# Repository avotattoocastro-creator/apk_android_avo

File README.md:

# Evidencia visual iPad

Run 46113092903 · commit 2692a683eb685c10ff76c8f7a6dec165fe4daa5a · rama develop/avo-performance-horse

Capturas del simulador iPad Pro 13 pulgadas (M4) con sesiones de DEMOSTRACIÓN sintéticas.

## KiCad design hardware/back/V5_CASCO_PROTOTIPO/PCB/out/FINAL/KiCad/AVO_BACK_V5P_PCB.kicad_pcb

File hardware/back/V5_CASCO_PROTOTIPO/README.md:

# AVO BACK V5 CASCO · PROTOTIPO A (URTK1.2 por tiras de pines)

**Decisión del usuario (18/11/2026):** antes de pagar la BETA con el ZED-F9P soldado (`../V5_CASCO`, REV B, ≈ 500 € por
el mínimo de 2 placas montadas), se prueba un **casco prototipo** con la misma electrónica pero con el GNSS en una placa
**URTK1.2** (ZED-F9P-04B, la misma del prototipo de la espalda) soldada encima. Si las pruebas son buenas se aprueba
este prototipo o se pasa a la REV B con el ZED integrado como BETA final.

**Estado:** NO VERIFICADO. Diseño en CI; nada fabricado ni impreso. Las cotas de la URTK1.2 salen del plano del anuncio
(y de `../V4/DOCS/INTEGRACION_GNSS.md`): **hay que medirlas con calibre antes de pedir** (ver «Comprobaciones»).

## Qué cambia frente a la REV B (`../V5_CASCO`)

| | REV B (BETA) | PROTOTIPO A |
|---|---|---|
| GNSS | ZED-F9P soldado (LGA), RF de antena en la placa | **URTK1.2** soldada sobre la cara B con 2 tiras de pines (9 + 10, paso 2,54, plástico 2,5 mm) |
| Antena | sobre la cara B de la PCB (plano 51 × 51) | sobre la URTK1.2, encima de una **placa de masa de 52 × 52 × 0,8** (cobre macizo), al U.FL J4 de la URTK1.2 |
| PCB | 51 × 51, tornillos a ±22 | **56 × 56, tornillos a ±24,5** (la URTK1.2 tapaba los de ±22) |
| Cápsula | 56,4 × 56,4 × 24,7 | **61,4 × 61,4 × ≈ 32,1** (≈ 35,6 sobre el casco) — estimado; el CI da la cifra exacta |
| Arranque en caliente del ZED | V_BCKP desde el carril siempre encendido | pila de respaldo de la URTK1.2 (J6) |
| Piezas quitadas | — | U1, R70, C71, L70, R71, D4, J5, C62, C64, C65 y el paso del coaxial H5 |
| Colocación | microSD a la derecha, pogo en el canto inferior | **WROOM en el centro-izquierda, microSD abajo en el centro (tarjeta por el canto inferior, entre D15 y D14), pogo en el canto SUPERIOR** (copa del pogo en la franja +Y del suelo de la cápsula) |
| LED y masa de la antena | 7 LED | **8 LED alineados** (D15/D14 bajo D10/D11; D17/D12 y D16/D13 a la misma altura) · **4 pines de masa J12–J15** en las esquinas, junto a la URTK1.2, soldados a la placa de masa |
| Resto | | igual: ESP32-S3-WROOM-1U-N16R8, cargador, táctil, anillo (**8 LED**: D14 vuelve, a la derecha de la salida de la tarjeta), MAX17048, LSM6DSV16X, microSD, pogo, Hall |

Firmware: **sin cambios de GPIO** (UART1 GPIO5/6, UART2 GPIO3/8, PPS GPIO7, RST GPIO9, ZED_EN GPIO10). El 3,3 V de la
URTK1.2 lo da el RT9080 (se apaga con ZED_EN), como el prototipo de la espalda desde la 3.10.x; 5V sin conectar.

## Conexiones de las tiras (marco de la URTK1.2, vista desde sus componentes)

| Tira | Pines | A la placa |
|---|---|---|
| J10 (9) | GND · 5V · 3V3 · TX2 · RX2 · CS · RX/MOSI · TX/MISO · SCK | GND · — · +3V3_ZED · GPIO3 (330 Ω) · GPIO8 (1 kΩ) · — · GPIO6 (1 kΩ) · GPIO5 (330 Ω) · — |
| J11 (10) | GND · 3V3 · SDA · SCL · FENCE · RTK · PPS · RST · SAFE · INT | GND · +3V3_ZED · — · — · — · — · GPIO7 (330 Ω) · GPIO9 (1 kΩ) · TP13 · — |

«—» = pad aislado: solo sujeta (más soldaduras contra la vibración del galope).

## Montaje
1. Desoldar el SMA J2 de la URTK1.2 (no cabe en la cápsula); la antena va a su U.FL **J4**.
2. Tiras de pines con el plástico **entre** las dos placas; soldar primero a la PCB, luego la URTK1.2 encima
   (componentes hacia arriba). Cortar las puntas a ras por las dos caras (≤ 1,5 mm en la cara F, a ras arriba).
3. Pines de masa J12–J15 (hilo de cobre de 1 mm o pin de tira, ≈ 15 mm) soldados en la PCB. **Placa de masa MACIZA**
   (sin recortes, 18/11 20:15) soldada a los 4 pines con su cara inferior a 5,5 mm sobre los componentes de la URTK1.2:
   pasa por encima de J6, J1, J3 y la clavija del U.FL. El cable de la antena sale de J4 hacia el canto y sube por el
   hueco entre la placa y la pared (≈ 2,3 mm).
4. Antena Taoglas AHP2258 sobre la placa de masa, en el cuadrado serigrafiado, con su cable al U.FL J4.

## Programar y desmontar sin soldar (19/11)
- **USB-C J16** (canto superior, cara F): programar y cargar con la placa **fuera de la cápsula**. El S3 entra solo en
  descarga por USB nativo; si un firmware lo desactiva, puentear TP2 (BOOT) a GND al arrancar. Mejor no conectar el USB-C y
  el pogo a la vez: desde el 23/11 el Schottky D18 impide que el 5 V del pogo entre en el ordenador, pero D± siguen
  en paralelo y el USB puede no enumerar.
- **Batería por coleta:** soldar una vez a BAT+ (J2) / BAT− (J6) un cable corto con conector JST PH 2.0 (el de la celda).
  El empalme va tumbado en la franja del fondo entre la batería y la pared, junto al costado por donde salen los hilos
  de la celda; sujetarlo con una gota de silicona o kapton (el PH no tiene pestillo). **Medir la polaridad** de la
  celda antes de enchufar: en las celdas chinas el rojo no siempre está en el mismo pin.

## Precauciones (revisión independiente 18/11)
- **Kapton** sobre la cara B de la PCB bajo la URTK1.2: las patas de J1, J6 y del SMA quitado apoyarían en la máscara
  sobre el plano de masa.
- **No conectar el USB-C (J1) de la URTK1.2 montada**: su LDO alimentaría +3V3_ZED con el ZED apagado por ZED_EN.
- **Pila J6:** usar la que pida la placa (si J6 se carga desde 3V3, una ML1220 recargable; nunca una CR1220).
- Pines de masa J12–J15: taladro 1,2 mm (pin de tira de 0,64 o hilo de cobre de hasta 1 mm).

## Comprobaciones antes de pedir nada (con la URTK1.2 en la mano)
- **Lo más importante:** medir CADA fila por separado: distancia del primer pin al canto del USB-C (supuesto 12,827 mm)
  y cuál es su pin GND. Si una fila empezara desde el otro canto, se desplazaría 2,54 mm y todas sus redes quedarían
  mal. Medidas de la placa (43,434 × 43,688) y distancia entre filas (40,64).
- Diámetro, altura y posición del portapilas J6 (el CAD supone Ø13 × 5 mm).
- Que **J4 llegue al ZED** con J2 quitado (continuidad / prueba con la antena).
- Altura del portapilas J6 con pila, de J1 (USB-C) y de J3, y lo que sobresale por debajo (debe ser < 2,5 mm).
- Versión del ZED en u-center (MON-VER): **ZED-F9P-04B**.

## Ficheros
- `PCB/fuente/` — generador (copia de la REV B con las diferencias marcadas «PROTOTIPO A»); las librerías grandes
  (`lib_easyeda`, `3d`, `hojas`) son enlaces a las de `../V5_CASCO/PCB/fuente`.
- `PCB/fuente/placa_masa.py` → `PCB/PLACA_MASA/`: Gerber y taladros de la placa de masa (2 capas, 0,8 mm) y su
  geometría para el CAD.
- `CAD/avo_casco_v5p.py` — cápsula; CI `build-back-v5p-cad.yml`. PCB: CI `build-back-v5p-pcb.yml`.

## Auditoría externa (22–23/11/2026)
- NTC RT2 sobre el centro de la batería, a 25,9 mm del BQ24072 (antes 3,0 mm: medía el calor del cargador).
- Anillo LED a 4,28 V (R25 620k / R26 100k), como la REV B: margen del DIN de 3,3 V ≈ 0,3 V.
- Schottky D18 (B5819W SL) en el VBUS del USB-C J16. Revisar su giro en la vista previa de JLC (cátodo = pad 1).
- Detalle: `docs/REGISTRO_DE_CAMBIOS.md` (23/11) y el documento de auditoría del proyecto.

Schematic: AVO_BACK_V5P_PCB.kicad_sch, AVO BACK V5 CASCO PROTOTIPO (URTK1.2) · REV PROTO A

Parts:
C18, C26, C27, C28, C36, C66, C67: 1u; C_0402_1005Metric; LCSC C52923
C19, C20, C21, C40, C60, C98: 10u 25V; C_0603_1608Metric; LCSC C96446
C22, C24, C35, C61, C99: 22u 10V; C_0805_2012Metric; LCSC C45783
C25, C34, C37, C38, C41, C42, C63, C68, C80, C90, C91, C92, C93, C94, C95, C96, C97: 100n; C_0402_1005Metric; LCSC C1525
C69: 22p; C_0402_1005Metric; LCSC C1555; not fitted
D2, D3: TVS 5 V; D_SOD-323; MPN PESD5V0S1BA; LCSC C2827694
D5, D6: BAT54C; SOT-23; MPN BAT54C; LCSC C2135
D10, D11, D12, D13, D14, D15, D16, D17: SK6812SIDE-A; AVO_SK6812SIDE-A_4.0x1.6mm; MPN SK6812SIDE-A (OPSCO); LCSC C5378721
D18: B5819W; D_SOD-123; MPN B5819W SL; LCSC C8598
F1, F2: PTC 1,5 A; Fuse_1206_3216Metric; MPN SMD1206P150TF; LCSC C20802
J2: BAT +; WirePad_D1.7_Drill0.9
J3: microSD DM3AT; microSD_HC_Hirose_DM3AT-SF-PEJM5; MPN DM3AT-SF-PEJM5; LCSC C114218
J6: BAT −; WirePad_D1.7_Drill0.9
J7: TÁCTIL; WirePad_D1.7_Drill0.9
J10: URTK1.2 9 pines; AVO_URTK1.2_Tira_1x09_P2.54
J11: URTK1.2 10 pines; AVO_URTK1.2_Tira_1x10_P2.54
J12, J13, J14, J15: GND PLACA ANTENA; WirePad_D2.0_Drill1.2
J16: USB-C programación; USB_C_Receptacle_HRO_TYPE-C-31-M-12; MPN TYPE-C-31-M-12 (HRO); LCSC C165948
L71: 1 µH; IND-SMD_L2.0-W1.6_FNR2016XXS; MPN WPN201610U1R0MT (Sunlord); LCSC C97016
P1: POGO VBUS; WirePad_D1.7_Drill0.9
P2: POGO D−; WirePad_D1.7_Drill0.9
P3: POGO D+; WirePad_D1.7_Drill0.9
P4: POGO GND; WirePad_D1.7_Drill0.9
P5: POGO AUX; WirePad_D1.7_Drill0.9
Q4, Q7: AO3401A; SOT-23; LCSC C15127
R6, R23: 1k5; R_0402_1005Metric; LCSC C25867
R7, R25: 2k; R_0402_1005Metric; LCSC C4109
R8, R9, R10, R13, R15, R21, R27, R40, R60: 100k; R_0402_1005Metric; LCSC C25741
R11, R17, R20, R41, R42, R43, R44, R45, R47: 10k; R_0402_1005Metric; LCSC C25744
R12: 68k; R_0402_1005Metric; LCSC C36871
R14, R32, R33: 1M; R_0402_1005Metric; LCSC C26083
R16, R22, R50, R51, R52: 1k; R_0402_1005Metric; LCSC C11702
R18, R19, R46: 22R; R_0402_1005Metric; LCSC C25092
R24, R26, R53, R54, R55: 330R; R_0402_1005Metric; LCSC C25104
R28, R29: 2k2; R_0402_1005Metric; LCSC C25879
R30, R31: 5k1; R_0402_1005Metric; LCSC C25905
RT2: NTC 10k B3380; R_0402_1005Metric; MPN NCP15XH103F03RC; LCSC C77131
TP1: EN; TestPoint_Pad_D1.0mm
TP2: BOOT; TestPoint_Pad_D1.0mm
TP3: GND; TestPoint_Pad_D1.0mm
TP4: TXD0; TestPoint_Pad_D1.0mm
TP5: RXD0; TestPoint_Pad_D1.0mm
TP6: 3V3; TestPoint_Pad_D1.0mm
TP7: VBAT; TestPoint_Pad_D1.0mm
TP8: VSYS; TestPoint_Pad_D1.0mm
TP9: 3V3_ZED; TestPoint_Pad_D1.0mm
TP10: 3V3_AON; TestPoint_Pad_D1.0mm
TP12: VLED; TestPoint_Pad_D1.0mm
TP13: SAFEBOOT; TestPoint_Pad_D1.0mm
U2: BQ24072RGTR; VQFN-16-1EP_3x3mm_P0.5mm_EP1.68x1.68mm_ThermalVias; MPN BQ24072RGTR; LCSC C140288
U3: TLV75733PDBVR; SOT-23-5; MPN TLV75733PDBVR; LCSC C485517
U4: ESP32-S3-WROOM-1U-N16R8; ESP32-S3-WROOM-1U; MPN ESP32-S3-WROOM-1U-N16R8; LCSC C3013946
U6: USBLC6-2SC6; SOT-23-6; LCSC C7519
U7: RT9080-33GJ5; SOT-23-5; MPN RT9080-33GJ5; LCSC C841192
U8: DRV5032FA; SOT-23; MPN DRV5032FADBZR; LCSC C140921
U9: XC6206P332MR; SOT-23; MPN XC6206P332MR-G (Torex); LCSC C5446
U10: TTP223-BA6-TD; SOT-23-6; MPN TTP223-BA6-TD (TDSEMIC); LCSC C42422127
U11: TPS61023DRLR; SOT-563_L1.6-W1.2-P0.50-LS1.6-BR; MPN TPS61023DRLR (TI); LCSC C919459
U12: MAX17048G+T10; TDFN-8_L2.0-W2.0-P0.50-BL-EP1.2; MPN MAX17048G+T10 (Analog Devices); LCSC C2682616
U13: LSM6DSV16X; ST_LGA-14L_2.5x3mm_P0.5mm; MPN LSM6DSV16XTR (ST); LCSC C5267406

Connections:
+3V3: C22.1, C24.1, C25.1, C26.1, C37.1, C38.1, C42.2, C80.1, Q4.2 (S), R9.2, R10.2, R11.2, R28.2, R29.2, R40.2, TP6.1, U3.5 (OUT), U4.2 (3V3), U8.1 (VCC), U13.5 (VDDIO), U13.8 (VDD), U13.12 (CS)
+3V3_AON: C67.1, C68.1, TP10.1, U9.2 (VOUT), U10.5 (VDD)
+3V3_SD: C40.1, C41.1, J3.4 (VDD), Q4.3 (D), R41.2, R42.2, R43.2, R44.2, R45.2
+3V3_ZED: C61.1, C63.1, J10.3 (3V3), J11.2 (3V3), TP9.1, U7.5 (VOUT)
BAT_ADC: C34.1, R32.2, R33.1, U4.38 (IO2 BAT_ADC)
BAT_F: F1.2, Q7.3 (D)
BAT_G: Q7.1 (G), R13.1
BAT_IN: F1.1, J2.1
BOOT: TP2.1, U4.27 (IO0 BOOT)
CHG_EN2: R8.1, U2.5 (EN2)
CHG_ILIM: R7.1, U2.12 (ILIM)
CHG_ISET: R6.1, U2.16 (ISET)
CHG_PG: R9.1, U2.7 (PGOOD), U4.31 (IO38 CHG_PG)
CHG_STAT: R10.1, U2.9 (CHG), U4.32 (IO39 CHG_STAT)
CHG_TMR: R12.1, U2.14 (TMR)
CHG_TS: RT2.1, U2.1 (TS)
EN: C27.1, R11.1, TP1.1, U4.3 (EN EN)
EN_3V3: C28.1, D5.3 (K), D6.3 (K), R14.1, U3.3 (EN)
GND: C18.2, C19.2, C20.2, C21.2, C22.2, C24.2, C25.2, C26.2, C27.2, C28.2, C34.2, C35.2, C36.2, C37.2, C38.2, C40.2, C41.2, C60.2, C61.2, C63.2, C66.2, C67.2, C68.2, C69.2, C80.2, C90.2, C91.2, C92.2, C93.2, C94.2, C95.2, C96.2, C97.2, C98.2, C99.2, D2.2 (A), D3.2 (A), D10.4 (GND), D11.4 (GND), D12.4 (GND), D13.4 (GND), D14.4 (GND), D15.4 (GND), D16.4 (GND), D17.4 (GND), J3.6 (VSS), J3.10 (DET_COM), J3.11 (SHELL), J6.1, J10.1 (GND), J11.1 (GND), J12.1, J13.1, J14.1, J15.1, J16.A1 (GND), J16.A12 (GND), J16.B1 (GND), J16.B12 (GND), J16.S1 (SHIELD), P4.1, R6.2, R7.2, R12.2, R13.2, R14.2, R15.2, R21.2, R23.2, R26.2, R27.2, R30.2, R31.2, R33.2, R60.2, RT2.2, TP3.1, U2.4 (CE), U2.6 (EN1), U2.8 (VSS), U2.15 (TD), U2.17 (EP), U3.2 (GND), U4.1 (GND), U4.40 (GND), U4.41 (GND), U6.2 (GND), U7.2 (GND), U8.3 (GND), U9.1 (VSS), U10.2 (VSS), U10.4 (AHLB), U10.6 (TOG), U11.4 (GND), U12.1 (CTG), U12.4 (GND), U12.6 (QSTRT), U12.9 (EP), U13.1 (SDO/SA0), U13.2 (SDx), U13.3 (SCx), U13.6 (GND), U13.7 (GND)
HALL: U4.39 (IO1 HALL), U8.2 (OUT)
I2C_SCL: R28.1, U4.34 (IO41 I2C_SCL), U12.7 (SCL), U13.13 (SCL)
I2C_SDA: R29.1, U4.35 (IO42 I2C_SDA), U12.8 (SDA), U13.14 (SDA)
IMU_INT1: U4.4 (IO4 IMU_INT1), U13.4 (INT1)
LED_D1: D10.1 (DIN), R24.2
LED_D2: D10.3 (DOUT), D11.1 (DIN)
LED_D3: D11.3 (DOUT), D12.1 (DIN)
LED_D4: D12.3 (DOUT), D13.1 (DIN)
LED_D5: D13.3 (DOUT), D14.1 (DIN)
LED_D6: D14.3 (DOUT), D15.1 (DIN)
LED_D7: D15.3 (DOUT), D16.1 (DIN)
LED_D8: D16.3 (DOUT), D17.1 (DIN)
LED_DIN_S3: R24.1, U4.24 (IO47 LED_DIN_S3)
LED_PWR: R27.1, U4.25 (IO48 LED_PWR), U11.2 (EN)
POGO_AUX: R20.2, R21.1, U4.33 (IO40 POGO_AUX)
POGO_AUX_C: D3.1 (K), P5.1, R20.1
POGO_VBUS: D2.1 (K), D18.1 (K), F2.1, P1.1
PWR_HOLD: D5.2 (A2), R15.1, U4.16 (IO46 PWR_HOLD)
S3_TX1: R50.1, U4.6 (IO6 S3_TX1)
S3_TX2: R51.1, U4.12 (IO8 S3_TX2)
S3_ZRST: R52.1, U4.17 (IO9 S3_ZRST)
SD_CLK: J3.5 (CLK), R46.2
SD_CLK0: R46.1, U4.20 (IO12 SD_CLK0)
SD_CMD: J3.3 (CMD), R41.1, U4.21 (IO13 SD_CMD)
SD_D0: J3.7 (DAT0), R42.1, U4.22 (IO14 SD_D0)
SD_D1: J3.8 (DAT1), R43.1, U4.8 (IO15 SD_D1)
SD_D2: J3.1 (DAT2), R44.1, U4.9 (IO16 SD_D2)
SD_D3: J3.2 (CD/DAT3), R45.1, U4.10 (IO17 SD_D3)
SD_G: C42.1, Q4.1 (G), R40.1, R47.2
SD_PWR_N: R47.1, U4.23 (IO21 SD_PWR_N)
TOUCH_E: J7.1, R16.1
TOUCH_I: C69.1, R16.2, U10.3 (I)
TOUCH_OUT: D5.1 (A1), R17.1, U10.1 (Q)
TOUCH_SENSE: R17.2, U4.19 (IO11 TOUCH_SENSE)
U0RX: TP5.1, U4.36 (RXD0 U0RX)
U0TX: TP4.1, U4.37 (TXD0 U0TX)
USBC_CC1: J16.A5 (CC1), R30.1
USBC_CC2: J16.B5 (CC2), R31.1
USBC_VBUS: D18.2 (A), J16.A4 (VBUS), J16.A9 (VBUS), J16.B4 (VBUS), J16.B9 (VBUS)
USB_DM: R19.2, U4.13 (IO19 D- USB_DM)
USB_DM_C: J16.A7 (D-), J16.B7 (D-), P2.1, R19.1, U6.3 (IO2), U6.4 (IO2)
USB_DP: R18.2, U4.14 (IO20 D+ USB_DP)
USB_DP_C: J16.A6 (D+), J16.B6 (D+), P3.1, R18.1, U6.1 (IO1), U6.6 (IO1)
VBAT: C20.1, C36.1, C66.1, Q7.2 (S), R32.1, TP7.1, U2.2 (BAT), U2.3 (BAT), U9.3 (VIN), U12.2 (CELL), U12.3 (VDD)
VBUS: C18.1, F2.2, R22.1, U2.13 (IN), U6.5 (VBUS)
VBUS_DET: D6.1 (A1), R22.2, R23.1, U4.11 (IO18 VBUS_DET)
VLED: C90.1, C91.1, C92.1, C93.1, C94.1, C95.1, C96.1, C97.1, C99.1, D10.2 (VDD), D11.2 (VDD), D12.2 (VDD), D13.2 (VDD), D14.2 (VDD), D15.2 (VDD), D16.2 (VDD), D17.2 (VDD), R25.1, TP12.1, U11.6 (VOUT)
VLED_FB: R25.2, R26.1, U11.1 (FB)
VLED_SW: L71.2, U11.5 (SW)
VSYS: C19.1, C21.1, C35.1, C60.1, C98.1, L71.1, R8.2, TP8.1, U2.10 (OUT), U2.11 (OUT), U3.1 (IN), U7.1 (VIN), U11.3 (VIN)
ZED_EN: R60.1, U4.18 (IO10 ZED_EN), U7.3 (EN)
ZED_PPS: R55.2, U4.7 (IO7 ZED_PPS)
ZED_PPS_C: J11.7 (PPS), R55.1
ZED_RST: J11.8 (RST), R52.2
ZED_RX1: J10.7 (RX/MOSI), R50.2
ZED_RX2: J10.5 (RX2), R51.2
ZED_SAFEBOOT: J11.9 (SAFE), TP13.1
ZED_TX1: R53.2, U4.5 (IO5 ZED_TX1)
ZED_TX1_C: J10.8 (TX/MISO), R53.1
ZED_TX2: R54.2, U4.15 (IO3 ZED_TX2)
ZED_TX2_C: J10.4 (TX2), R54.1

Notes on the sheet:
POGO MAGNÉTICO DE 5 CONTACTOS (por hilos): VBUS · D− · D+ · GND · AUX — carga y USB con el PC · ESD
ENCENDIDO Y APAGADO TOTAL: OR de diodos al EN del 3,3 V (táctil · POWER_HOLD GPIO46 · VBUS)
ANILLO DE LUZ: 7 × SK6812SIDE-A (GPIO47) a 4,3 V con elevador TPS61023 (EN = GPIO48, salida desconectada con EN = 0)
microSD (SDMMC 4 bits) · alimentación conmutada
GNSS EN MÓDULO URTK1.2 (ZED-F9P) POR TIRAS DE PINES: 3,3 V propio con EN (RT9080) · UART1 · UART2 · PPS · RESET
BATERÍA (hilos soldados) · PTC · medida por ADC
CARGADOR CON CAMINO DE POTENCIA (BQ24072) · batería 1S ≥ 2000 mAh
3,3 V PRINCIPAL (TLV75733P, 1 A) · EN = OR(táctil, POWER_HOLD, VBUS)
ESP32-S3-WROOM-1U-N16R8 (16 MB + PSRAM 8 MB) · BLE móvil + ESP-NOW cinchas · arranque
SENSOR HALL DRV5032 · encendido al poner la cápsula en la base del casco
3,3 V SIEMPRE ENCENDIDO (XC6206, ≈ 1 µA): táctil (la URTK1.2 lleva su pila de respaldo)
TÁCTIL SELLADO (TTP223, activo alto, directo) · electrodo por hilo · lectura en GPIO11
MEDIDOR DE BATERÍA MAX17048 (0x36, ModelGauge, ≈ 3 µA)
IMU LSM6DSV16X (0x6A) · INT1 → GPIO4 (despierta por movimiento)
BUS I²C (GPIO41 SCL · GPIO42 SDA, 400 kHz)
PUNTOS DE PRUEBA
Generado por fuente/avo_back_v5_pcb.py (mismo origen de datos que la placa). Las conexiones son etiquetas globales: dos pines con la misma etiqueta están unidos.

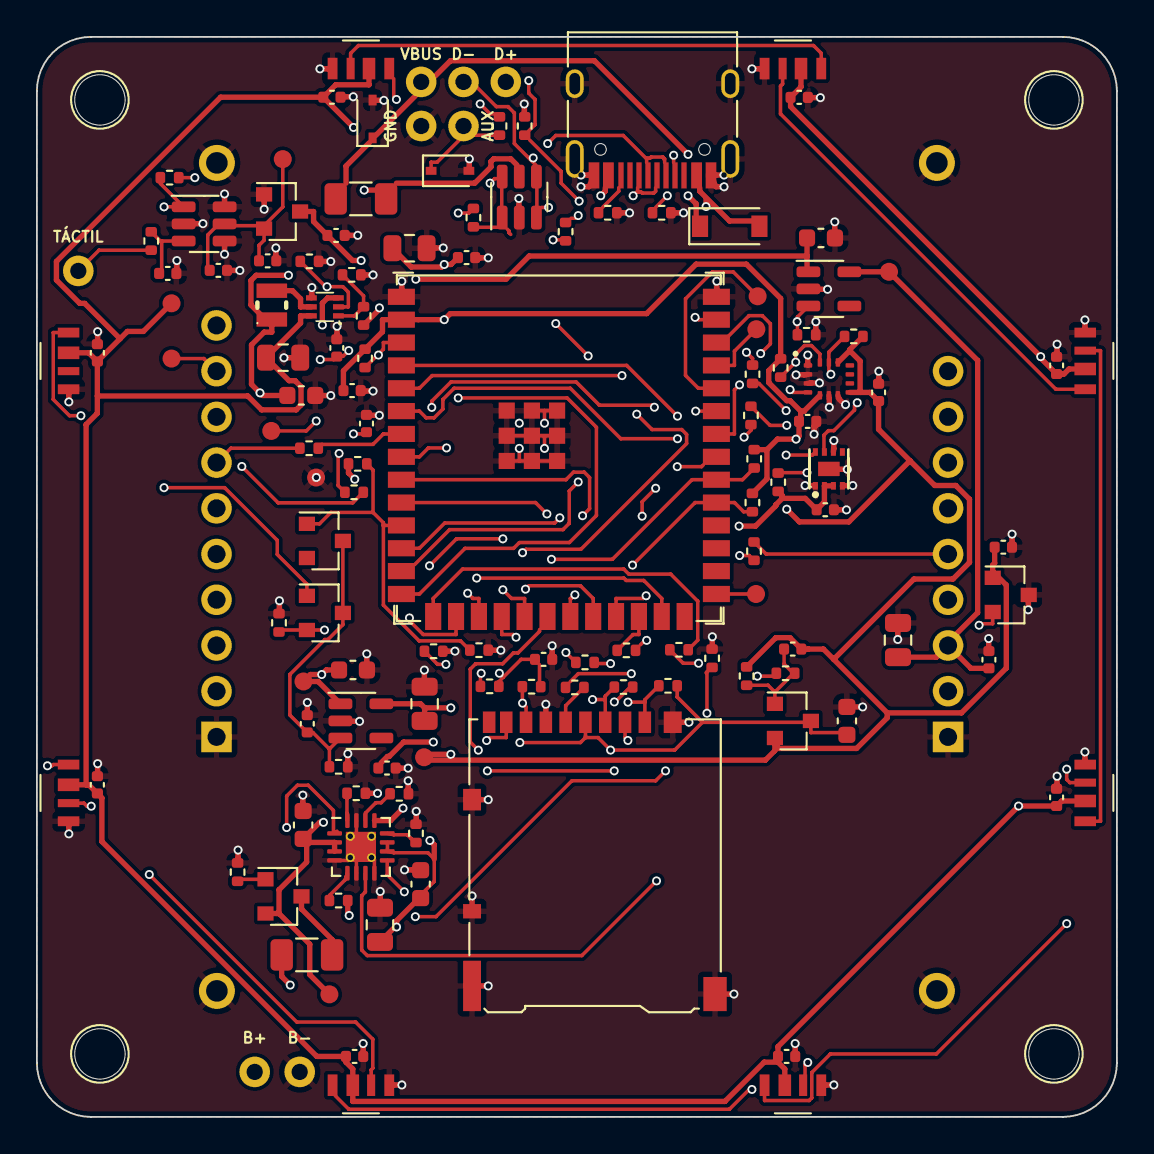
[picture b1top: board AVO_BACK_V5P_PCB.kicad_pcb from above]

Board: 4 copper layers, 60.0 x 60.0 mm, 141 parts (0 on the bottom side), 80 nets.

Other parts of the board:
H1, H2, H3, H4: TALADRO M2,5; AVO_Taladro_NPTH_D2.8

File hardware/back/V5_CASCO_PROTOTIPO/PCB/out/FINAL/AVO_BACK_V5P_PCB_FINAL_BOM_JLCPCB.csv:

Comment,Designator,Footprint,LCSC Part #
"PTC 1,5 A","F1,F2",Fuse_1206_3216Metric,C20802
TVS 5 V,"D2,D3",D_SOD-323,C2827694
10k,"R11,R17,R20,R41,R42,R43,R44,R45,R47",R_0402_1005Metric,C25744
100k,"R8,R9,R10,R13,R15,R21,R22,R26,R27,R40,R60",R_0402_1005Metric,C25741
USBLC6-2SC6,U6,SOT-23-6,C7519
USB-C programación,J16,USB_C_Receptacle_HRO_TYPE-C-31-M-12,C165948
B5819W,D18,D_SOD-123,C8598
5k1,"R30,R31",R_0402_1005Metric,C25905
22R,"R18,R19,R46",R_0402_1005Metric,C25092
150k,R23,R_0402_1005Metric,C25755
BQ24072RGTR,U2,VQFN-16-1EP_3x3mm_P0.5mm_EP1.68x1.68mm_ThermalVias,C140288
1u,"C18,C26,C27,C28,C36,C66,C67",C_0402_1005Metric,C52923
10u 25V,"C19,C20,C21,C40,C60,C98",C_0603_1608Metric,C96446
22u 10V,"C22,C24,C35,C61,C99",C_0805_2012Metric,C45783
1k5,R6,R_0402_1005Metric,C25867
2k,R7,R_0402_1005Metric,C4109
NTC 10k B3380,RT2,R_0402_1005Metric,C77131
68k,R12,R_0402_1005Metric,C36871
AO3401A,"Q4,Q7",SOT-23,C15127
1M,"R14,R32,R33",R_0402_1005Metric,C26083
100n,"C25,C34,C37,C38,C41,C42,C63,C68,C80,C90,C91,C92,C93,C94,C95,C96,C97",C_0402_1005Metric,C1525
TLV75733PDBVR,U3,SOT-23-5,C485517
BAT54C,"D5,D6",SOT-23,C2135
XC6206P332MR,U9,SOT-23,C5446
TTP223-BA6-TD,U10,SOT-23-6,C42422127
1k,"R16,R50,R51,R52",R_0402_1005Metric,C11702
RT9080-33GJ5,U7,SOT-23-5,C841192
330R,"R24,R53,R54,R55",R_0402_1005Metric,C25104
ESP32-S3-WROOM-1U-N16R8,U4,ESP32-S3-WROOM-1U,C3013946
SK6812SIDE-A,"D10,D11,D12,D13,D14,D15,D16,D17",AVO_SK6812SIDE-A_4.0x1.6mm,C5378721
TPS61023DRLR,U11,easyeda2kicad:SOT-563_L1.6-W1.2-P0.50-LS1.6-BR,C919459
1 µH,L71,easyeda2kicad:IND-SMD_L2.0-W1.6_FNR2016XXS,C97016
620k,R25,R_0402_1005Metric,C137952
DRV5032FA,U8,SOT-23,C140921
microSD DM3AT,J3,microSD_HC_Hirose_DM3AT-SF-PEJM5,C114218
2k2,"R28,R29",R_0402_1005Metric,C25879
MAX17048G+T10,U12,easyeda2kicad:TDFN-8_L2.0-W2.0-P0.50-BL-EP1.2,C2682616
LSM6DSV16X,U13,ST_LGA-14L_2.5x3mm_P0.5mm,C5267406
